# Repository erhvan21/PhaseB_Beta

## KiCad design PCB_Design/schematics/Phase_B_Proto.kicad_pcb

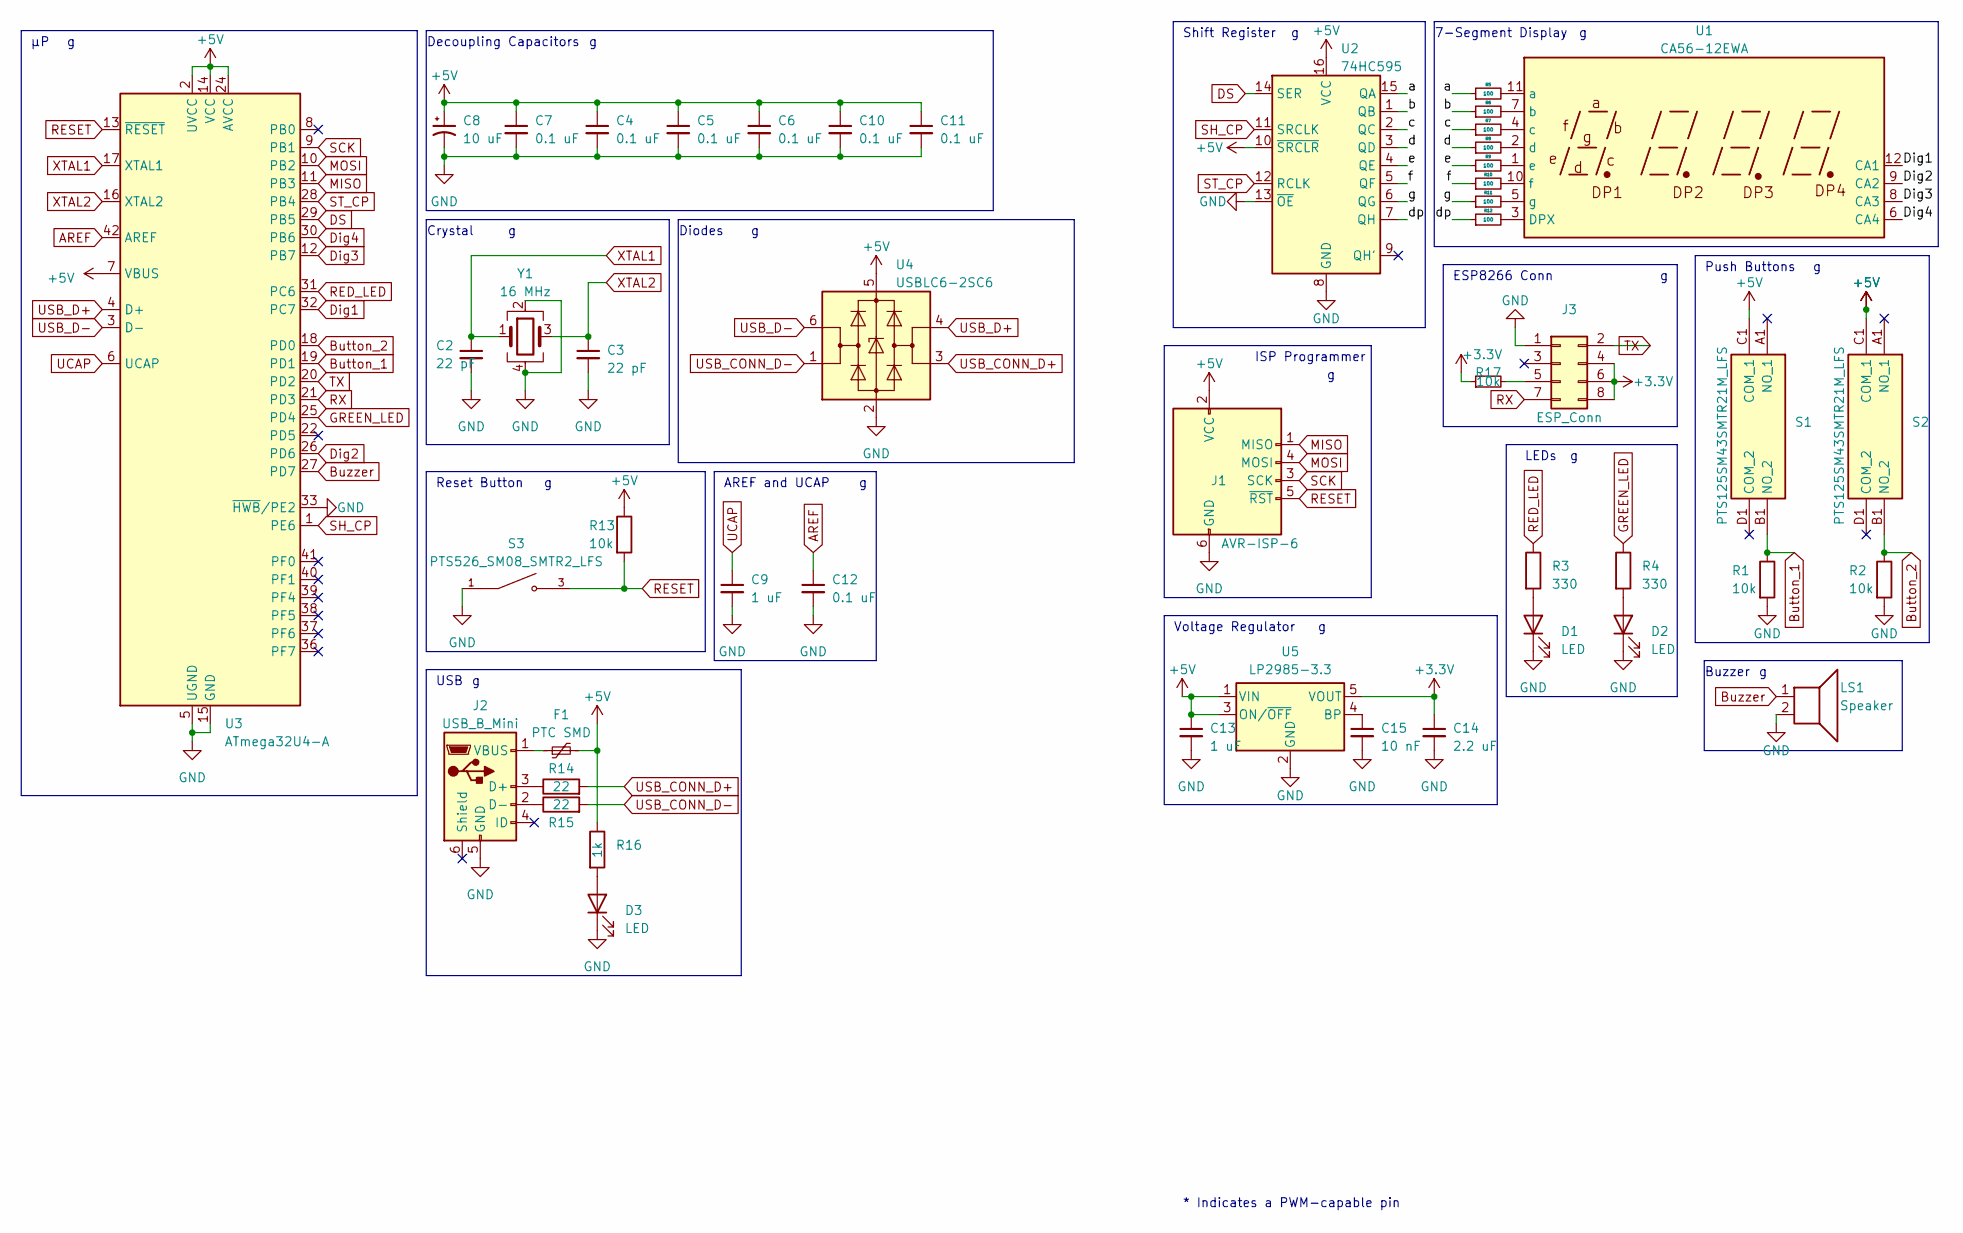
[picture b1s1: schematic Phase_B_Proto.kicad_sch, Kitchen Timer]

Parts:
C2, C3: 22 pF; C_0603_1608Metric
C4, C5, C6, C7, C10, C11, C12: 0.1 uF; C_0603_1608Metric
C8: 10 uF; C_0805_2012Metric
C9, C13: 1 uF; C_0603_1608Metric
C14: 2.2 uF; C_0603_1608Metric
C15: 10 nF; C_0603_1608Metric
D1, D2, D3: LED; LED_0805_2012Metric
F1: PTC SMD; Fuse_1812_4532Metric
J1: AVR-ISP-6; PinSocket_2x03_P2.54mm_Vertical
J2: USB_B_Mini; USB_Mini-B_Lumberg_2486_01_Horizontal
J3: ESP_Conn; PinSocket_2x04_P2.54mm_Vertical
LS1: Speaker; Buzzer_12x9.5RM7.6
R1, R2: 10k; R_0805_2012Metric
R3, R4: 330; R_0805_2012Metric
R5, R6, R7, R8, R9, R10, R11, R12: 100; R_0805_2012Metric
R13, R17: 10k; R_0603_1608Metric
R14, R15: 22; R_0603_1608Metric
R16: 1k; R_0805_2012Metric
S1, S2: PTS125SM43SMTR21M_LFS; PTS125_SMD_Button; Manufacturer_Part_Number PTS125SM43SMTR21M LFS; Mouser Part Number 611-PTS125S43SMTRLFS
S3: PTS526_SM08_SMTR2_LFS; PTS526_SMD_Button; PARTREV 20 mar 19
U1: CA56-12EWA
U2: 74HC595; TSSOP-16_4.4x5mm_P0.65mm
U3: ATmega32U4-A; TQFP-44_10x10mm_P0.8mm
U4: USBLC6-2SC6; SOT-23-6
U5: LP2985-3.3; SOT-23-5
Y1: 16 MHz; Crystal_SMD_Abracon_ABM8G-4Pin_3.2x2.5mm

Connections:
+3.3V: C14.1, J3.4, J3.6, J3.8, R17.1, U5.5 (VOUT)
+5V: C4.1, C5.1, C6.1, C7.1, C8.1, C10.1, C11.1, C13.1, F1.2, J1.2 (VCC), R13.1, R16.1, S1.C1 (COM_1), S2.C1 (COM_1), U2.10 (~SRCLR), U2.16 (VCC), U3.2 (UVCC), U3.7 (VBUS), U3.14 (VCC), U3.24 (AVCC), U3.34 (VCC), U3.44 (AVCC), U4.5 (VBUS), U5.1 (VIN), U5.3 (ON/~OFF)
/a: R5.1, U2.15 (QA)
/b: R6.1, U2.1 (QB)
/c: R7.1, U2.2 (QC)
/d: R8.1, U2.3 (QD)
/dp: R12.1, U2.7 (QH)
/e: R9.1, U2.4 (QE)
/f: R10.1, U2.5 (QF)
/g: R11.1, U2.6 (QG)
AREF: C12.1, U3.42 (AREF)
Button_1: R1.1, S1.B1 (NO_2), U3.19 (PD1)
Button_2: R2.1, S2.B1 (NO_2), U3.18 (PD0)
Buzzer: LS1.1, U3.27 (PD7)
DS: U2.14 (SER), U3.29 (PB5)
Dig1: U1.12 (CA1), U3.32 (PC7)
Dig2: U1.9 (CA2), U3.26 (PD6)
Dig3: U1.8 (CA3), U3.12 (PB7)
Dig4: U1.6 (CA4), U3.30 (PB6)
GND: C2.2, C3.2, C4.2, C5.2, C6.2, C7.2, C8.2, C9.2, C10.2, C11.2, C12.2, C13.2, C14.2, C15.2, D1.1 (K), D2.1 (K), D3.1 (K), J1.6 (GND), J2.5 (GND), J3.1, LS1.2, R1.2, R2.2, S3.1, U2.8 (GND), U2.13 (~OE), U3.5 (UGND), U3.15 (GND), U3.23 (GND), U3.33 (~HWB/PE2), U3.35 (GND), U3.43 (GND), U4.2 (GND), U5.2 (GND), Y1.2, Y1.4
GREEN_LED: R4.1, U3.25 (PD4)
MISO: J1.1 (MISO), U3.11 (PB3)
MOSI: J1.4 (MOSI), U3.10 (PB2)
unnamed: D1.2 (A), R3.2
unnamed: D2.2 (A), R4.2
unnamed: D3.2 (A), R16.2
unnamed: J2.3 (D+), R14.1
unnamed: J2.2 (D-), R15.1
unnamed: F1.1, J2.1 (VBUS)
unnamed: J3.5, R17.2
unnamed: R12.2, U1.3 (DPX)
unnamed: R5.2, U1.11 (a)
unnamed: R6.2, U1.7 (b)
unnamed: R7.2, U1.4 (c)
unnamed: R8.2, U1.2 (d)
unnamed: R9.2, U1.1 (e)
unnamed: R10.2, U1.10 (f)
unnamed: R11.2, U1.5 (g)
unnamed: C15.1, U5.4 (BP)
RED_LED: R3.1, U3.31 (PC6)
RESET: J1.5 (~RST), R13.2, S3.3, U3.13 (~RESET)
RX: J3.7, U3.21 (PD3)
SCK: J1.3 (SCK), U3.9 (PB1)
SH_CP: U2.11 (SRCLK), U3.1 (PE6)
ST_CP: U2.12 (RCLK), U3.28 (PB4)
TX: J3.2, U3.20 (PD2)
UCAP: C9.1, U3.6 (UCAP)
USB_CONN_D+: R14.2, U4.3 (I/O2)
USB_CONN_D-: R15.2, U4.1 (I/O1)
USB_D+: U3.4 (D+), U4.4 (I/O2)
USB_D-: U3.3 (D-), U4.6 (I/O1)
XTAL1: C2.1, U3.17 (XTAL1), Y1.1
XTAL2: C3.1, U3.16 (XTAL2), Y1.3

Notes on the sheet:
ISP Programmer
Voltage Regulator
USB
Diodes
AREF and UCAP
LEDs
Push Buttons
Reset Button
Decoupling Capacitors
Shift Register
* Indicates a PWM-capable pin
Crystal
ESP8266 Conn
7-Segment Display
Buzzer

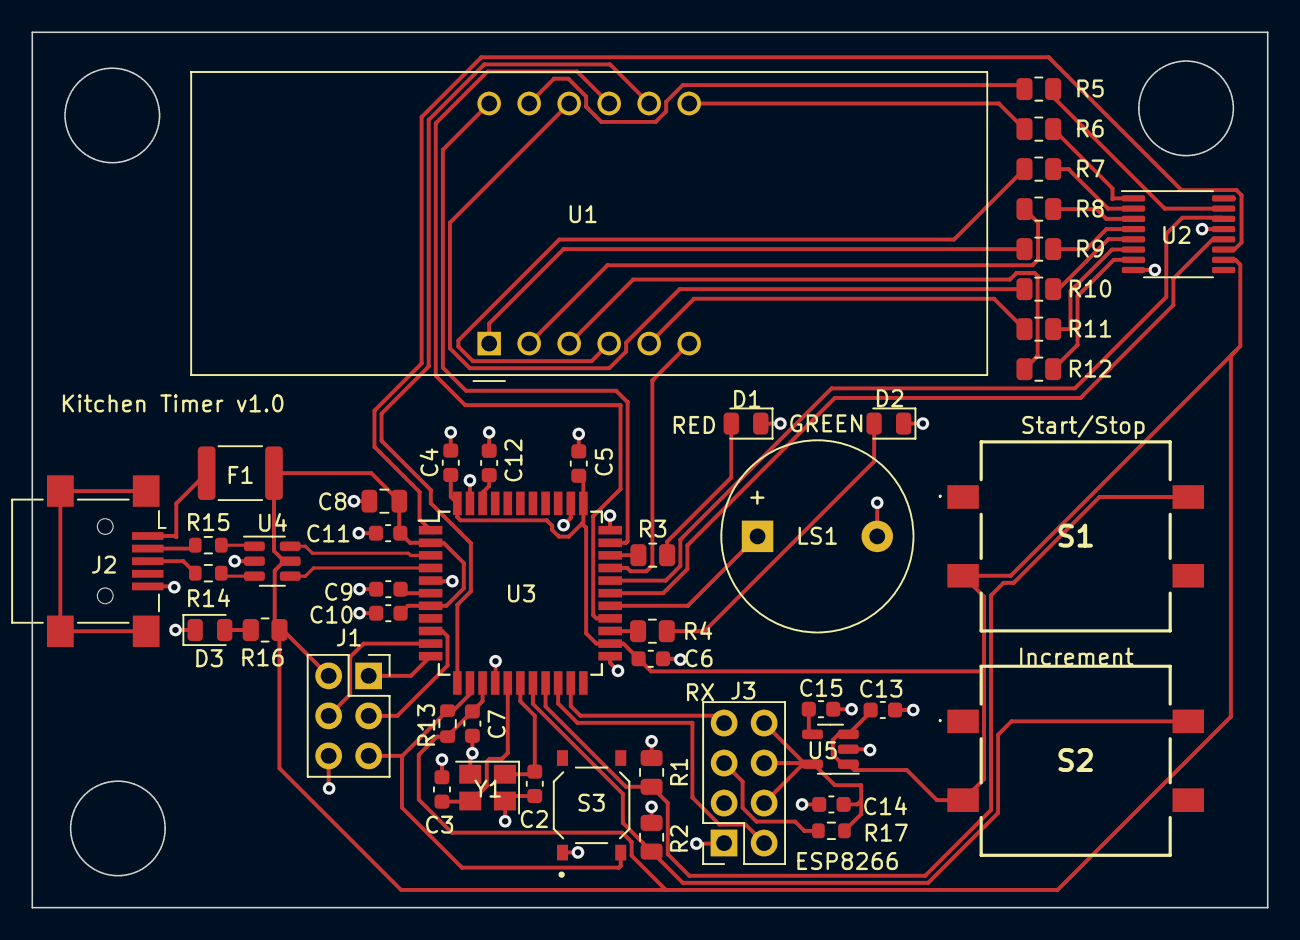
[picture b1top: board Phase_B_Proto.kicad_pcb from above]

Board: 2 copper layers, 78.4 x 55.6 mm, 48 parts (0 on the bottom side), 53 nets.

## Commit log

2023-06-08 Initial Push before final edits
2023-06-08 push 2
2023-06-08 summary
